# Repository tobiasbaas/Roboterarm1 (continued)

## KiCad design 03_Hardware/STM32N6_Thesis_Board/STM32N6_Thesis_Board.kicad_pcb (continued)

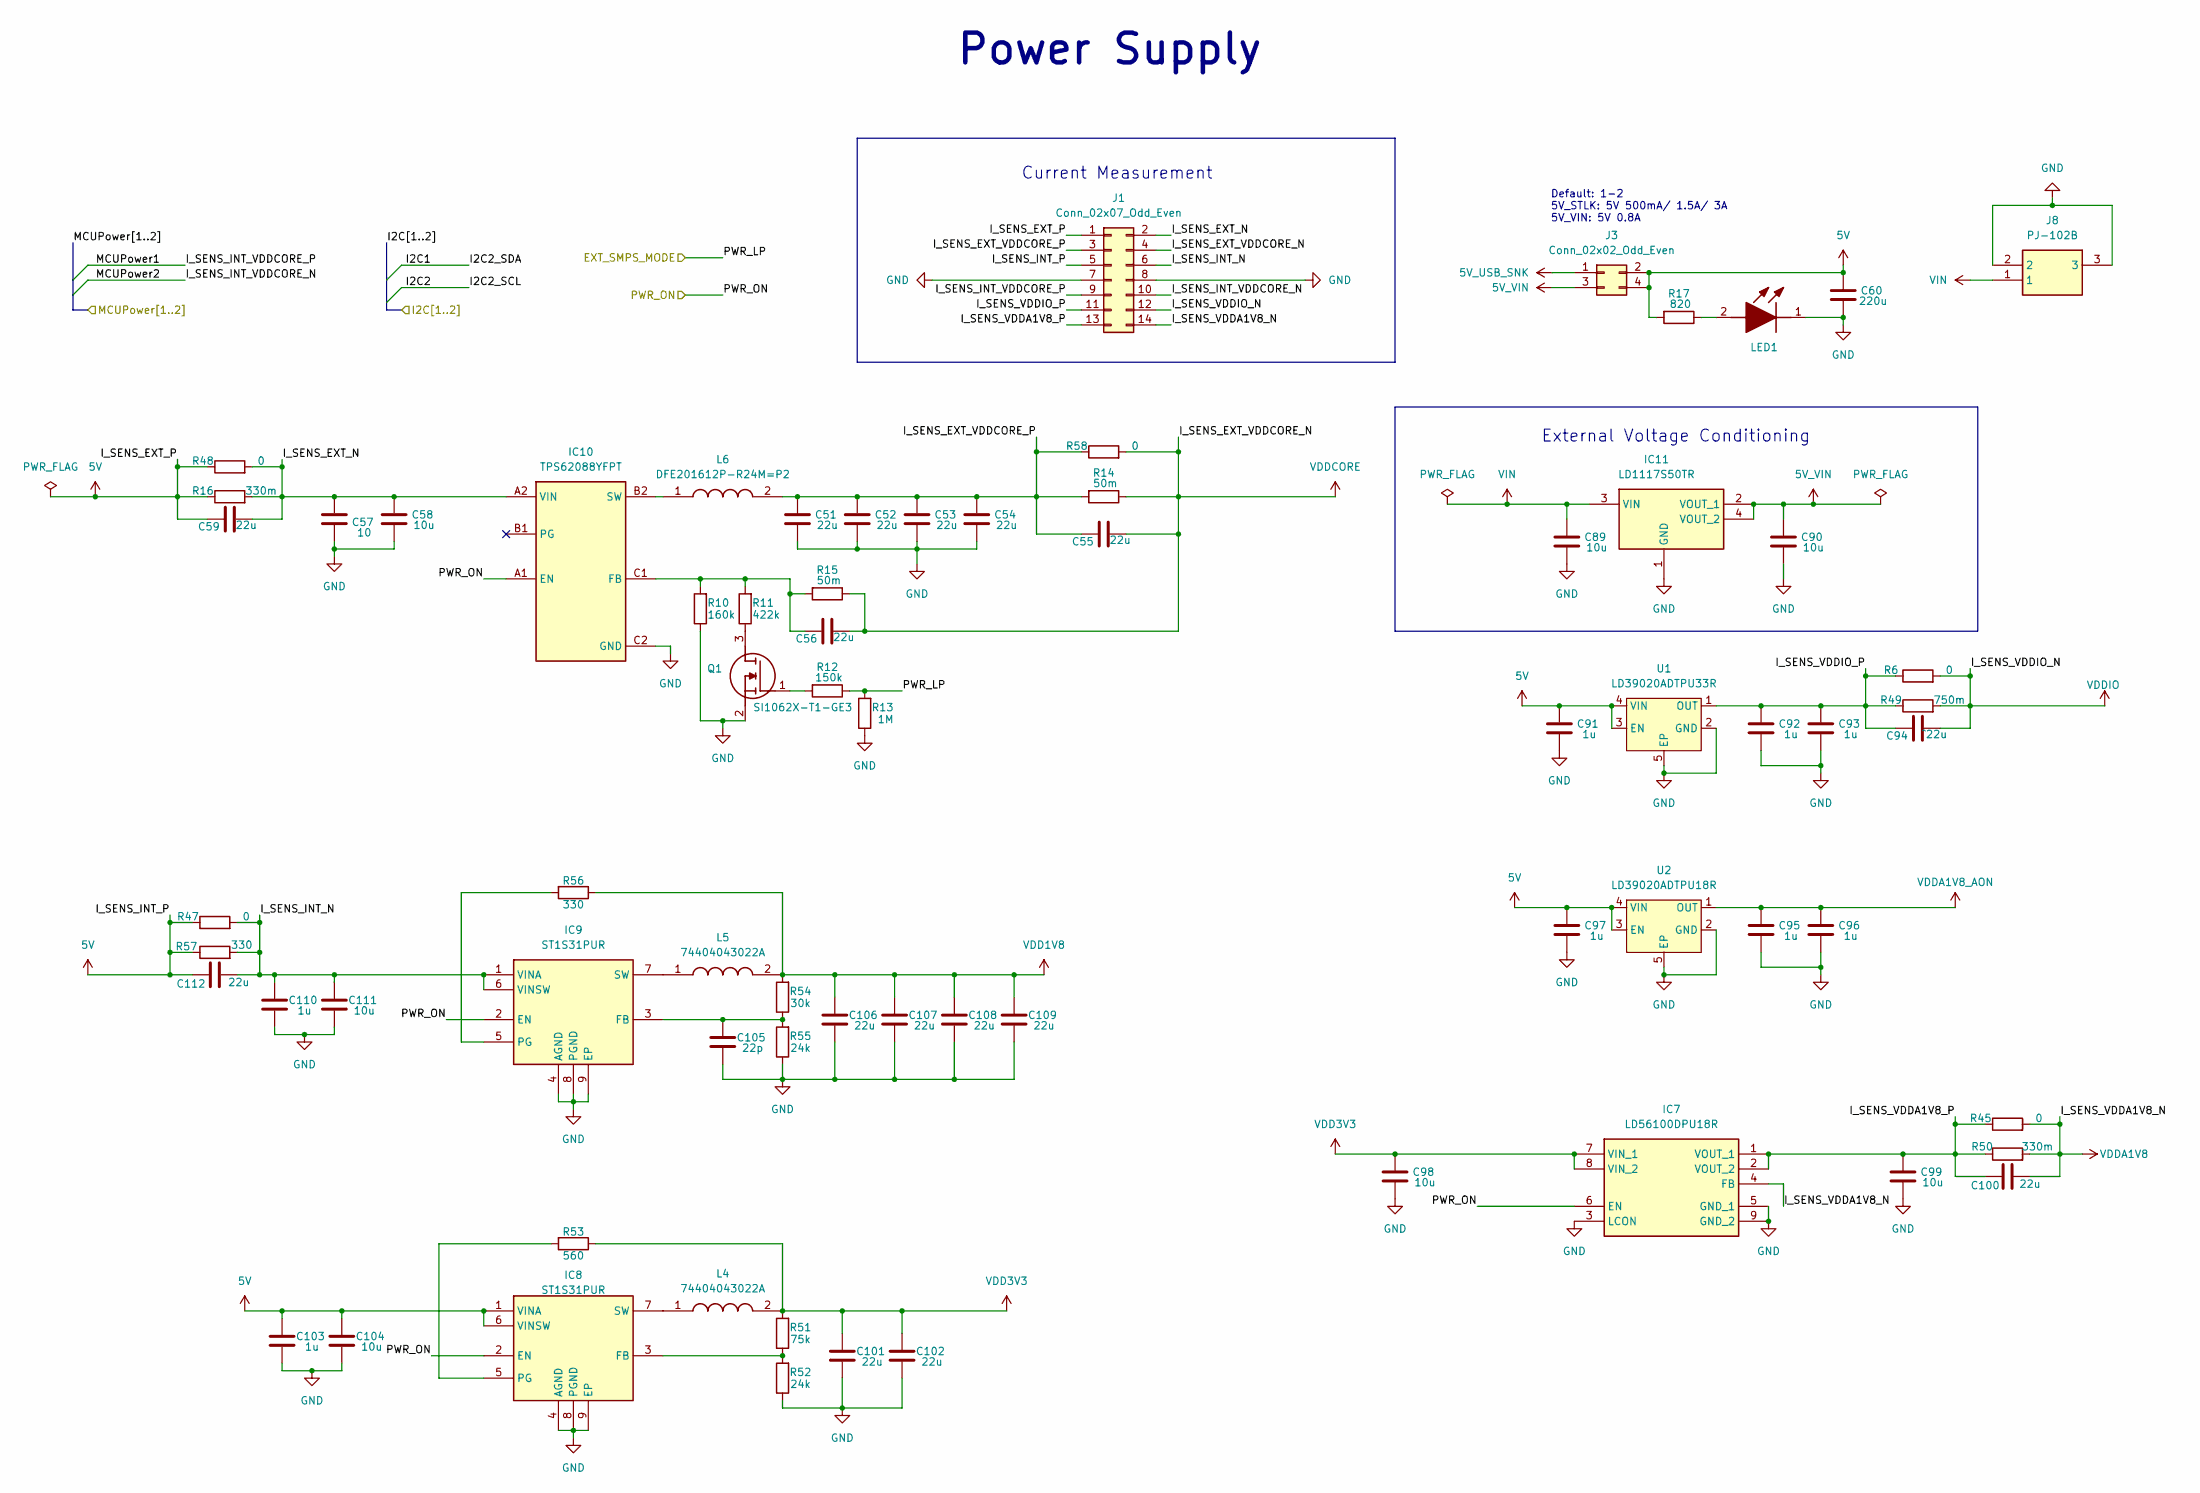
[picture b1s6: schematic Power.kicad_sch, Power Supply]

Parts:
C51, C52, C53, C54, C55, C56, C59, C100, C101, C102, C106, C107, C108, C109, C112: 22u; C_0603_1608Metric
C57: 10; C_0603_1608Metric
C58, C89, C90, C98, C99, C104, C111: 10u; C_0603_1608Metric
C60: 220u; C_0603_1608Metric
C91, C92, C93, C95, C96, C97, C103, C110: 1u; C_0603_1608Metric
C94: ^22u; C_0603_1608Metric
C105: 22p; C_0603_1608Metric
IC7: LD56100DPU18R; Mouser Part Number 511-LD56100DPU18R
IC8, IC9: ST1S31PUR; SON65P300X300X100-9N-D; Mouser Part Number 511-ST1S31PUR
IC10: TPS62088YFPT; BGA6C40P2X3_80X120X50; Mouser Part Number 595-TPS62088YFPT
IC11: LD1117S50TR; SOT230P700X190-4N; Mouser Part Number 511-LD1117S50
J1: Conn_02x07_Odd_Even; PinHeader_2x07_P2.54mm_Vertical
J3: Conn_02x02_Odd_Even; PinHeader_2x02_P2.54mm_Vertical
J8: PJ-102B; PJ102B; Mouser Part Number 490-PJ-102B
L4, L5: 74404043022A; INDPM4040X250N; Mouser Part Number 710-74404043022A
L6: DFE201612P-R24M=P2; 1286ASH1R0MP2; Mouser Part Number 81-DFE201612P-R24MP2
LED1: KG_EELP41.22-PHRH-35-A8J8-20-R18; KGEELP4122PHRH35A8J820R18; Mouser Part Number 720-P4122PHRH35A8J82
Q1: SI1062X-T1-GE3; SOTFL50P160X80-3N; Mouser Part Number 78-SI1062X-T1-GE3
R6, R45, R47, R48, R58: 0; R_0603_1608Metric
R10: 160k; R_0603_1608Metric
R11: 422k; R_0603_1608Metric
R12: 150k; R_0603_1608Metric
R13: 1M; R_0603_1608Metric
R14, R15: 50m; R_0603_1608Metric
R16, R50: 330m; R_0603_1608Metric
R17: 820; R_0603_1608Metric
R49: 750m; R_0603_1608Metric
R51: 75k; R_0603_1608Metric
R52, R55: 24k; R_0603_1608Metric
R53: 560; R_0603_1608Metric
R54: 30k; R_0603_1608Metric
R56, R57: 330; R_0603_1608Metric
U1: LD39020ADTPU33R; OnSemi_XDFN4-1EP_1.0x1.0mm_EP0.52x0.52mm
U2: LD39020ADTPU18R; OnSemi_XDFN4-1EP_1.0x1.0mm_EP0.52x0.52mm

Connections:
5V: C59.2, C60.2, C91.2, C97.2, C103.2, C104.2, C112.2, IC8.1 (VINA), IC8.6 (VINSW), J1.1, J1.5, J3.2, J3.4, R16.1, R17.2, R47.1, R48.1, R57.1, U1.3 (EN), U1.4 (VIN), U2.3 (EN), U2.4 (VIN); also elsewhere on the board
5V_USB_SNK: J3.1; also elsewhere on the board
5V_VIN: C90.2, IC11.2 (VOUT_1), IC11.4 (VOUT_2), J3.3
/Power/I_SENS_EXT_N: C57.2, C58.2, C59.1, IC10.A2 (VIN), J1.2, R16.2, R48.2
/Power/I_SENS_EXT_VDDCORE_P: C51.2, C52.2, C53.2, C54.2, C55.2, J1.3, L6.2, R14.2, R58.1
/Power/I_SENS_INT_N: C110.2, C111.2, C112.1, IC9.1 (VINA), IC9.6 (VINSW), J1.6, R47.2, R57.2
/Power/I_SENS_VDDA1V8_P: C99.2, C100.2, IC7.1 (VOUT_1), IC7.2 (VOUT_2), J1.13, R45.1, R50.1
/Power/I_SENS_VDDIO_P: C92.2, C93.2, C94.2, J1.11, R6.1, R49.1, U1.1 (OUT)
/Power/MCUPower1: J1.9; also elsewhere on the board
/Power/PWR_LP: R12.1, R13.2; also elsewhere on the board
/Power/PWR_ON: IC7.6 (EN), IC8.2 (EN), IC9.2 (EN), IC10.A1 (EN); also elsewhere on the board
GND: C51.1, C52.1, C53.1, C54.1, C57.1, C58.1, C60.1, C89.1, C90.1, C91.1, C92.1, C93.1, C95.1, C96.1, C97.1, C98.1, C99.1, C101.1, C102.1, C103.1, C104.1, C105.1, C106.1, C107.1, C108.1, C109.1, C110.1, C111.1, IC7.3 (LCON), IC7.5 (GND_1), IC7.9 (GND_2), IC8.4 (AGND), IC8.8 (PGND), IC8.9 (EP), IC9.4 (AGND), IC9.8 (PGND), IC9.9 (EP), IC10.C2 (GND), IC11.1 (GND), J1.7, J1.8, J8.2, J8.3, LED1.1 (K), Q1.2 (S), R10.1, R13.1, R52.1, R55.1, U1.2 (GND), U1.5 (EP), U2.2 (GND), U2.5 (EP); also elsewhere on the board
unnamed: IC8.3 (FB), R51.1, R52.2
unnamed: IC8.5 (PG), R53.2
unnamed: IC8.7 (SW), L4.1
unnamed: C105.2, IC9.3 (FB), R54.1, R55.2
unnamed: IC9.5 (PG), R56.2
unnamed: IC9.7 (SW), L5.1
unnamed: C56.2, IC10.C1 (FB), R10.2, R11.2, R15.2
unnamed: IC10.B2 (SW), L6.1
unnamed: LED1.2 (A), R17.1
unnamed: Q1.3 (D), R11.1
unnamed: Q1.1 (G), R12.2
VDD1V8: C106.2, C107.2, C108.2, C109.2, L5.2, R54.2, R56.1; also elsewhere on the board
VDD3V3: C98.2, C101.2, C102.2, IC7.7 (VIN_1), IC7.8 (VIN_2), L4.2, R51.2, R53.1; also elsewhere on the board
VDDA1V8: C100.1, IC7.4 (FB), J1.14, R45.2, R50.2; also elsewhere on the board
VDDA1V8_AON: C95.2, C96.2, U2.1 (OUT); also elsewhere on the board
VDDCORE: C55.1, C56.1, J1.4, J1.10, R14.1, R15.1, R58.2; also elsewhere on the board
VDDIO: C94.1, J1.12, R6.2, R49.2; also elsewhere on the board
VIN: C89.2, IC11.3 (VIN), J8.1

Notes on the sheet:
Current Measurement
Power Supply
Default: 1-2 5V_STLK: 5V 500mA/ 1.5A/ 3A 5V_VIN: 5V 0.8A
External Voltage Conditioning

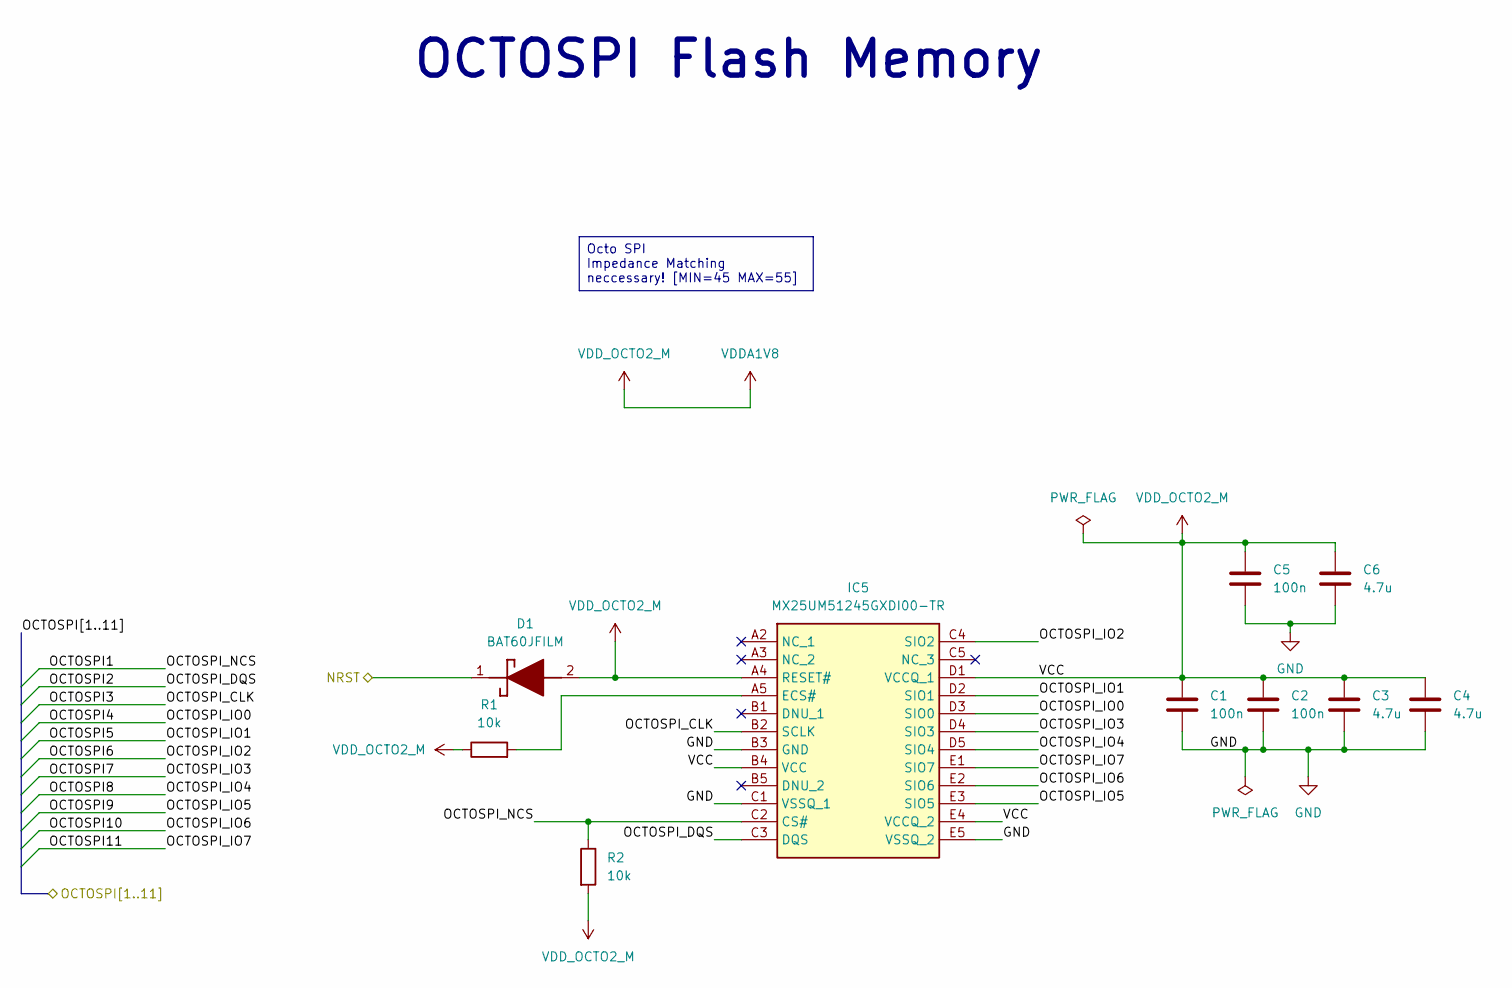
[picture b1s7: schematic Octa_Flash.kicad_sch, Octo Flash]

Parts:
C1, C2, C5: 100n; C_0603_1608Metric
C3, C4, C6: 4.7u; C_0603_1608Metric
D1: BAT60JFILM; SOD2513X117N; Mouser Part Number 511-BAT60JFILM
IC5: MX25UM51245GXDI00-TR; BGA24C100P5X5_600X800X120; Mouser Part Number 95-25UM51245GXDITR
R1, R2: 10k; R_0603_1608Metric

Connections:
/External Interface/NRST: D1.1 (K); also elsewhere on the board
/Octa_Flash/OCTOSPI1: IC5.C2 (CS#), R2.1; also elsewhere on the board
/Octa_Flash/OCTOSPI2: IC5.C3 (DQS); also elsewhere on the board
/Octa_Flash/OCTOSPI3: IC5.B2 (SCLK); also elsewhere on the board
/Octa_Flash/OCTOSPI4: IC5.D3 (SIO0); also elsewhere on the board
/Octa_Flash/OCTOSPI5: IC5.D2 (SIO1); also elsewhere on the board
/Octa_Flash/OCTOSPI6: IC5.C4 (SIO2); also elsewhere on the board
/Octa_Flash/OCTOSPI7: IC5.D4 (SIO3); also elsewhere on the board
/Octa_Flash/OCTOSPI8: IC5.D5 (SIO4); also elsewhere on the board
/Octa_Flash/OCTOSPI9: IC5.E3 (SIO5); also elsewhere on the board
/Octa_Flash/OCTOSPI10: IC5.E2 (SIO6); also elsewhere on the board
/Octa_Flash/OCTOSPI11: IC5.E1 (SIO7); also elsewhere on the board
GND: C1.2, C2.2, C3.2, C4.2, C5.2, C6.2, IC5.B3 (GND), IC5.C1 (VSSQ_1), IC5.E5 (VSSQ_2); also elsewhere on the board
unnamed: IC5.A5 (ECS#), R1.2
VDDA1V8: C1.1, C2.1, C3.1, C4.1, C5.1, C6.1, D1.2 (A), IC5.A4 (RESET#), IC5.B4 (VCC), IC5.D1 (VCCQ_1), IC5.E4 (VCCQ_2), R1.1, R2.2; also elsewhere on the board

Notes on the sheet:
OCTOSPI Flash Memory
Octo SPI Impedance Matching neccessary! [MIN=45 MAX=55]

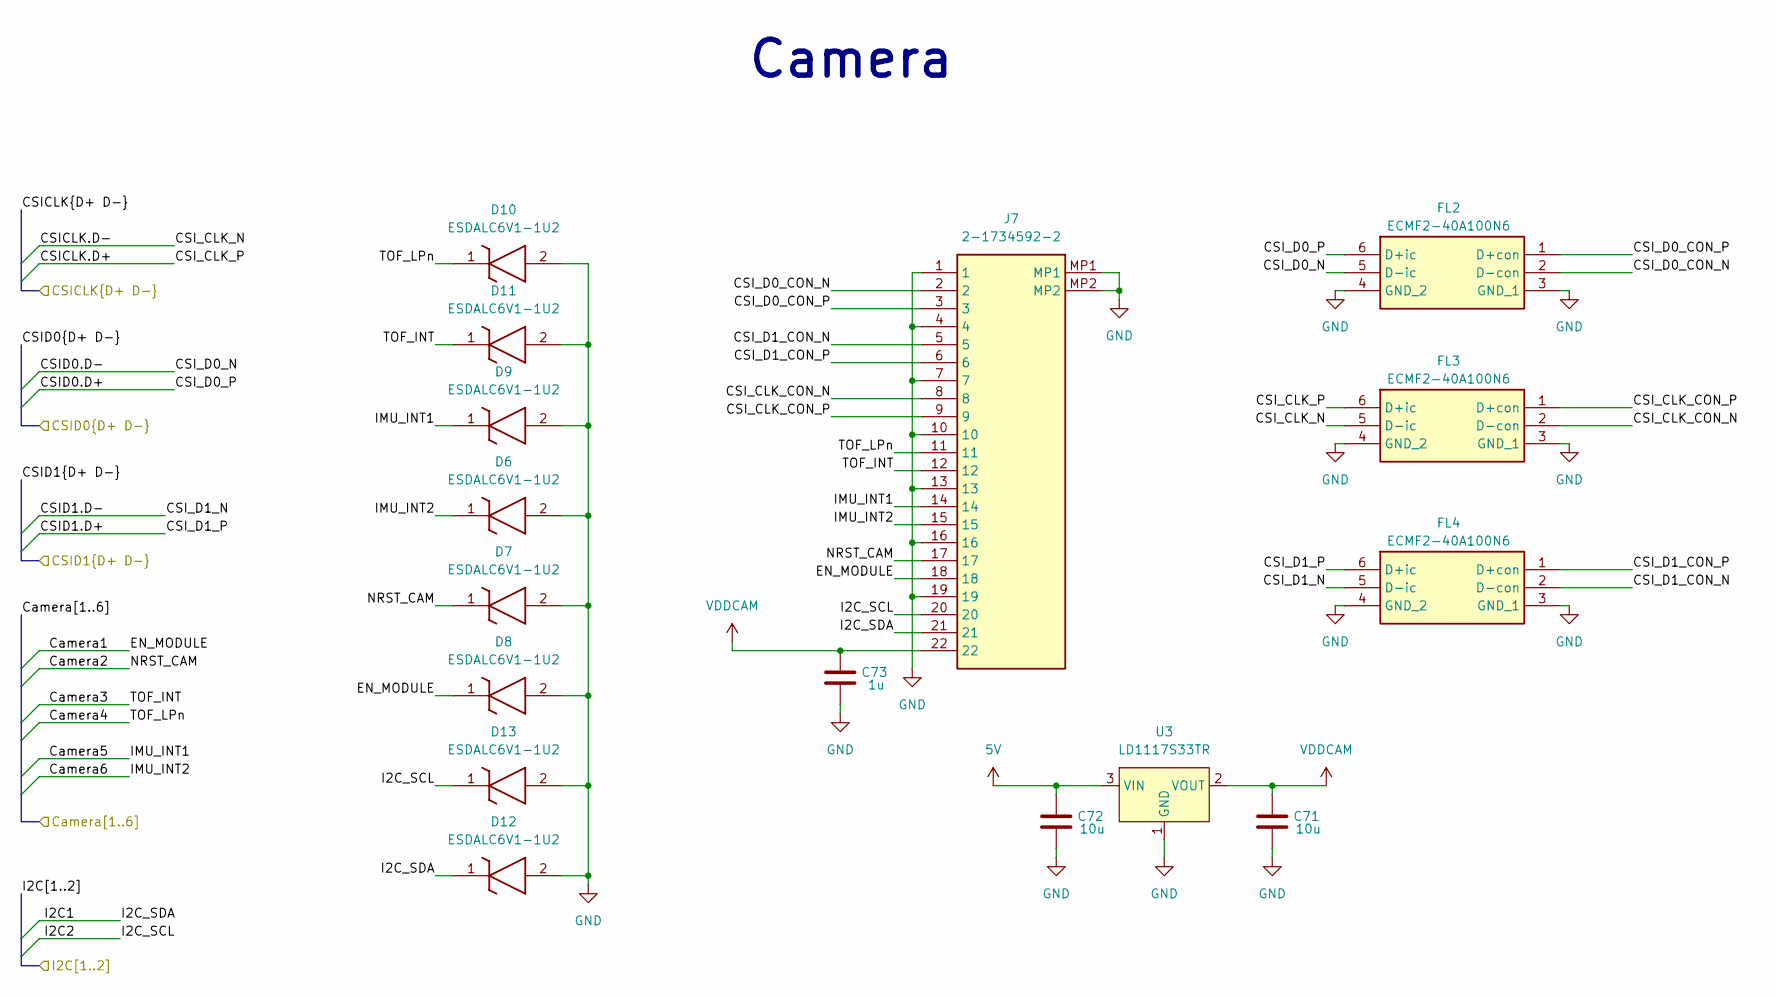
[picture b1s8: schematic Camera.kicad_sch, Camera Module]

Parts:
C71, C72: 10u; C_0603_1608Metric
C73: 1u; C_0603_1608Metric
D6, D7, D8, D9, D10, D11, D12, D13: ESDALC6V1-1U2; ESDALC6V11U2; Mouser Part Number 511-ESDALC6V1-1U2
FL2, FL3, FL4: ECMF2-40A100N6; ECMF240A100N6; Mouser Part Number 511-ECMF2-40A100N6
J7: 2-1734592-2; 217345922; Mouser Part Number 571-2-1734592-2
U3: LD1117S33TR; SOT-223-3_TabPin2

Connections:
5V: C72.2, U3.3 (VIN); also elsewhere on the board
/Camera/CSICLK.D+: FL3.6 (D+ic); also elsewhere on the board
/Camera/CSICLK.D-: FL3.5 (D-ic); also elsewhere on the board
/Camera/CSID0.D+: FL2.6 (D+ic); also elsewhere on the board
/Camera/CSID0.D-: FL2.5 (D-ic); also elsewhere on the board
/Camera/CSID1.D+: FL4.6 (D+ic); also elsewhere on the board
/Camera/CSID1.D-: FL4.5 (D-ic); also elsewhere on the board
/Camera/CSI_CLK_CON_N: FL3.2 (D-con), J7.8
/Camera/CSI_CLK_CON_P: FL3.1 (D+con), J7.9
/Camera/CSI_D0_CON_N: FL2.2 (D-con), J7.2
/Camera/CSI_D0_CON_P: FL2.1 (D+con), J7.3
/Camera/CSI_D1_CON_N: FL4.2 (D-con), J7.5
/Camera/CSI_D1_CON_P: FL4.1 (D+con), J7.6
/Camera/Camera3: D11.1 (K), J7.12; also elsewhere on the board
/Camera/Camera4: D10.1 (K), J7.11; also elsewhere on the board
/Camera/Camera5: D9.1 (K), J7.14; also elsewhere on the board
/Camera/Camera6: D6.1 (K), J7.15; also elsewhere on the board
/Camera/I2C1: D12.1 (K), J7.21; also elsewhere on the board
/Camera/I2C2: D13.1 (K), J7.20; also elsewhere on the board
GND: C71.1, C72.1, C73.1, D6.2 (A), D7.2 (A), D8.2 (A), D9.2 (A), D10.2 (A), D11.2 (A), D12.2 (A), D13.2 (A), FL2.3 (GND_1), FL2.4 (GND_2), FL3.3 (GND_1), FL3.4 (GND_2), FL4.3 (GND_1), FL4.4 (GND_2), J7.1, J7.4, J7.7, J7.10, J7.13, J7.16, J7.19, J7.MP1, J7.MP2, U3.1 (GND); also elsewhere on the board
VDDCAM: C71.2, C73.2, D7.1 (K), D8.1 (K), J7.17, J7.18, J7.22, U3.2 (VOUT); also elsewhere on the board

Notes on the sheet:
Camera

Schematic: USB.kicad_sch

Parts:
C65: 2.2u; C_0603_1608Metric
C66, C67: 330p; C_0603_1608Metric
C68: 100n; C_0603_1608Metric
C69: 10p; C_0603_1608Metric
D2: ESDA25P35-1U1M; ESDA25P351U1M; Mouser Part Number 511-ESDA25P35-1U1M
FL1: ECMF2-40A100N6; ECMF240A100N6; Mouser Part Number 511-ECMF2-40A100N6
IC2: TCPP03-M20; QFN50P400X400X80-21N-D; Mouser Part Number 511-TCPP03-M20
J4: 12401826E412A; Mouser Part Number 523-12401826E412A
LED2: KG_EELP41.22-PHRH-35-A8J8-20-R18; KGEELP4122PHRH35A8J820R18; Mouser Part Number 720-P4122PHRH35A8J82
LED3: LS_R976-NR-1; LEDC2012X40N; Mouser Part Number 720-LSR976-NR-1
Q2, Q5: STL40DN3LLH5; Mouser Part Number 511-STL40DN3LLH5
Q3, Q4: BSR14; SOT95P240X120-3N; Mouser Part Number 512-BSR14
R20, R27, R32: 10k; R_0603_1608Metric
R21, R26, R35: 100k; R_0603_1608Metric
R22: 24k; R_0603_1608Metric
R23, R25: 1.3M; R_0603_1608Metric
R24, R33: 22m; R_0603_1608Metric
R28, R34: 47k; R_0603_1608Metric
R29: 22k; R_0603_1608Metric
R30: 270; R_0603_1608Metric
R31: 140k; R_0603_1608Metric
R60, R61: 0; R_0603_1608Metric

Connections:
5V: Q5.5 (D1_1), Q5.6 (D1_2); also elsewhere on the board
5V_USB_SNK: Q2.5 (D1_1), Q2.6 (D1_2); also elsewhere on the board
/Camera/I2C1: R61.1; also elsewhere on the board
/Camera/I2C2: R60.1; also elsewhere on the board
/STM32N6_microcontroller/USB1: IC2.20 (EN), R26.2; also elsewhere on the board
/STM32N6_microcontroller/USB1HS.D+: FL1.6 (D+ic); also elsewhere on the board
/STM32N6_microcontroller/USB1HS.D-: FL1.5 (D-ic); also elsewhere on the board
/STM32N6_microcontroller/USB2: IC2.4 (IANA); also elsewhere on the board
/STM32N6_microcontroller/USB3: IC2.1 (CC1); also elsewhere on the board
/STM32N6_microcontroller/USB4: IC2.3 (CC2); also elsewhere on the board
/STM32N6_microcontroller/USB5: IC2.19 (FLGN), R27.1; also elsewhere on the board
/STM32N6_microcontroller/USB6: C69.2, R31.1, R32.2; also elsewhere on the board
/STM32N6_microcontroller/USB7: R34.1; also elsewhere on the board
/USB/D+: FL1.1 (D+con), J4.A6 (D+_1), J4.B6 (D+_2)
/USB/D-: FL1.2 (D-con), J4.A7 (D-_1), J4.B7 (D-_2)
GND: C65.1, C66.1, C67.1, C68.1, C69.1, D2.2 (A), FL1.3 (GND_1), FL1.4 (GND_2), IC2.12 (GND), IC2.21 (EP), J4.A1 (GND_1), J4.A12 (GND_2), J4.B1 (GND_3), J4.B12 (GND_4), J4.MH1, J4.MH2, J4.MH3, J4.MH4, Q3.2 (E), Q4.2 (E), R20.1, R22.2, R26.1, R29.2, R32.1, R35.2; also elsewhere on the board
unnamed: C68.2, IC2.14 (CBIAS)
unnamed: C66.2, IC2.15 (CC1C), J4.A5 (CC1)
unnamed: C67.2, IC2.13 (CC2C), J4.B5 (CC2)
unnamed: IC2.7 (GDCG), Q2.2 (G2), Q2.4 (G1), R25.1
unnamed: IC2.8 (GDCS), Q2.1 (S2), Q2.3 (S1), R25.2
unnamed: IC2.5 (GDPG), Q5.2 (G2), Q5.4 (G1), R23.1
unnamed: IC2.6 (GDPS), Q5.1 (S2), Q5.3 (S1), R23.2
unnamed: IC2.16 (I2C_ADD), R20.2
unnamed: IC2.10 (ISENSE), Q2.7 (D2_1), Q2.8 (D2_2), Q5.7 (D2_1), Q5.8 (D2_2), R24.2
unnamed: IC2.18 (SCL), R60.2
unnamed: IC2.17 (SDA), R61.2
unnamed: IC2.11 (VSENSE), R21.2, R22.1
unnamed: LED2.2 (A), R30.1
unnamed: LED2.1 (K), Q3.3 (C)
unnamed: LED3.2 (A), R33.2
unnamed: LED3.1 (K), Q4.3 (C)
unnamed: Q3.1 (B), R28.2, R29.1
unnamed: Q4.1 (B), R34.2, R35.1
VBUS: C65.2, D2.1 (K), IC2.9 (VBUSC), J4.A4 (VBUS_1), J4.A9 (VBUS_2), J4.B4 (VBUS_3), J4.B9 (VBUS_4), R21.1, R24.1, R28.1, R31.2
VDD3V3: IC2.2 (VCC_VCONN), R30.2, R33.1; also elsewhere on the board
VDDIO: R27.2; also elsewhere on the board

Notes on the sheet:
<- Sink Path
Diff Pair
5V_USB_LED
VBUS_SENSE
USB
Source Path ->
USB DP/DM should be routed in 90 ohm dff +/-10%

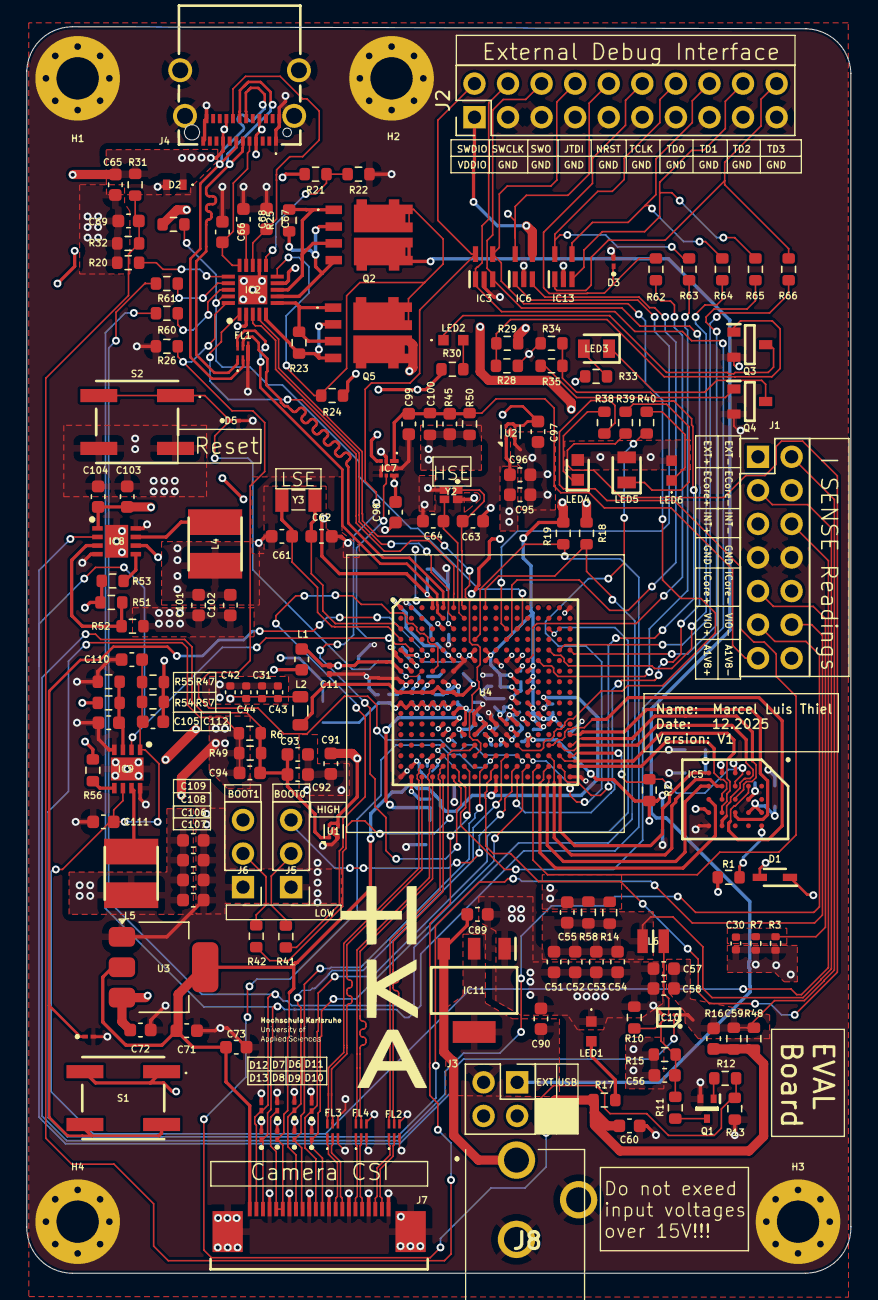
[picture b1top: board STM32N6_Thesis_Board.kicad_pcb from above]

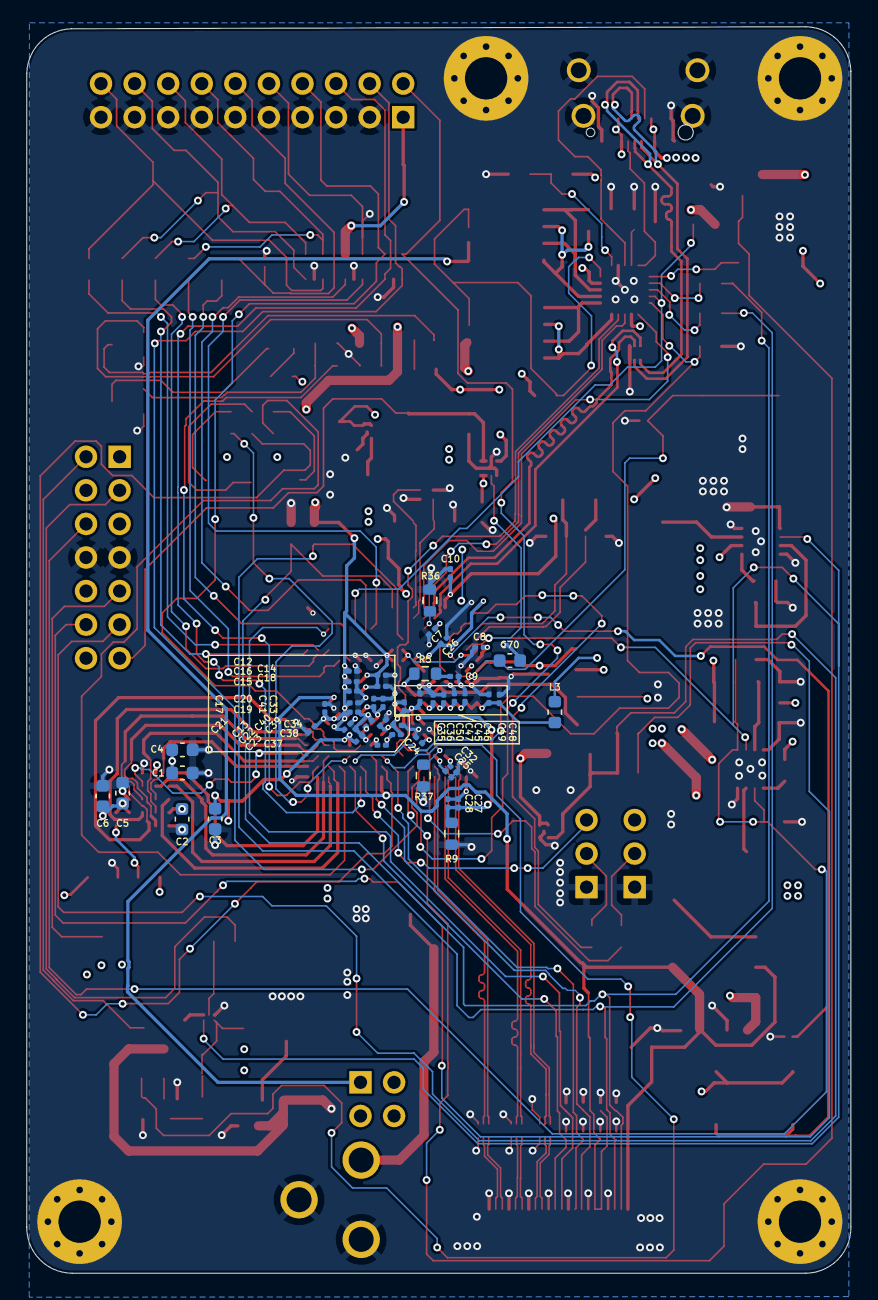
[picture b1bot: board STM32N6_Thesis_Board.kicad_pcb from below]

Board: 4 copper layers, 62.3 x 94.3 mm, 220 parts (49 on the bottom side), 131 nets.

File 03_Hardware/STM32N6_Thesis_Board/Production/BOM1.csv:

ID;Bezeichner;Footprint;Stückzahl;Bezeichnung;Anbieter und Referenz
1;FL3,FL2,FL1,FL4;ECMF240A100N6;4;ECMF2-40A100N6;
2;R50,R16;R_0603_1608Metric;2;330m;
3;R49;R_0603_1608Metric;1;750m;
4;R22,R55,R52;R_0603_1608Metric;3;24k;
5;R1,R32,R42,R41,R20,R2,R27,R5;R_0603_1608Metric;8;10k;
6;R66,R61,R6,R64,R60,R65,R47,R48,R63,R58,R45,R62,R9;R_0603_1608Metric;13;0;
7;U1;OnSemi_XDFN4-1EP_1.0x1.0mm_EP0.52x0.52mm;1;LD39020ADTPU33R;
8;C105;C_0603_1608Metric;1;22p;
9;R17;R_0603_1608Metric;1;820;
10;C106,C52,C53,C100,C109,C51,C102,C54,C59,C112,C108,C107,C101,C55,C56;C_0603_1608Metric;15;22u;
11;IC10;BGA6C40P2X3_80X120X50;1;TPS62088YFPT;
12;C96,C97,C91,C95,C93,C73,C103,C110,C92;C_0603_1608Metric;9;1u;
13;C42,C43,C30,C31,C44;C_0402_1005Metric;5;22u;
14;Q2,Q5;STL40DN3LLH5;2;STL40DN3LLH5;
15;R39,R57,R38,R40,R56;R_0603_1608Metric;5;330;
16;L6;1286ASH1R0MP2;1;DFE201612P-R24M=P2;
17;L2;L_0805_2012Metric;1;74479276168;
18;R18,R19;R_0603_1608Metric;2;1.5k;
19;C67,C66;C_0603_1608Metric;2;330p;
20;R3;R_0402_1005Metric;1;0;
21;IC9,IC8;SON65P300X300X100-9N-D;2;ST1S31PUR;
22;J4;12401826E412A;1;12401826E412A;
23;Q4,Q3;SOT95P240X120-3N;2;BSR14;
24;R53;R_0603_1608Metric;1;560;
25;C99,C89,C58,C98,C90,C104,C71,C111,C72;C_0603_1608Metric;9;10u;
26;D8,D10,D5,D3,D7,D4,D6,D9,D13,D11,D12;ESDALC6V11U2;11;ESDALC6V1-1U2;
27;R24,R33;R_0603_1608Metric;2;22m;
28;U4;BGA264C80P17X17_1400X1400X100;1;STM32N657X0H3Q;
29;IC11;SOT230P700X190-4N;1;LD1117S50TR;
30;J2;PinHeader_2x10_P2.54mm_Horizontal;1;Conn_02x10_Odd_Even;
31;J3;PinHeader_2x02_P2.54mm_Vertical;1;Conn_02x02_Odd_Even;
32;L4,L5;INDPM4040X250N;2;74404043022A;
33;R11;R_0603_1608Metric;1;422k;
34;R23,R25;R_0603_1608Metric;2;1.3M;
35;Q1;SOTFL50P160X80-3N;1;SI1062X-T1-GE3;
36;C57;C_0603_1608Metric;1;10;
37;R7;R_0402_1005Metric;1;50m;
38;J6,J5;PinHeader_1x03_P2.54mm_Vertical;2;Conn_01x03;
39;C61,C62;C_0603_1608Metric;2;2.2p;
40;R34,R28;R_0603_1608Metric;2;47k;
41;D1;SOD2513X117N;1;BAT60JFILM;
42;LED5,LED3;LEDC2012X40N;2;LS_R976-NR-1;
43;C65;C_0603_1608Metric;1;2.2u;
44;R29;R_0603_1608Metric;1;22k;
45;R51;R_0603_1608Metric;1;75k;
46;R21,R26,R35;R_0603_1608Metric;3;100k;
47;R54;R_0603_1608Metric;1;30k;
48;LED2,LED1,LED6;KGEELP4122PHRH35A8J820R18;3;KG_EELP41.22-PHRH-35-A8J8-20-R18;
49;C94;C_0603_1608Metric;1;22u;
50;R30;R_0603_1608Metric;1;270;
51;R15,R14;R_0603_1608Metric;2;50m;
52;C60;C_0603_1608Metric;1;220u;
53;U3;SOT-223-3_TabPin2;1;LD1117S33TR;
54;IC3,IC6,IC13;SOT65P210X110-5N;3;ESDALC6V1W5;
55;R10;R_0603_1608Metric;1;160k;
56;S1,S2;KSC721JLFS;2;KSC721J_LFS;
57;J1;PinHeader_2x07_P2.54mm_Vertical;1;Conn_02x07_Odd_Even;
58;IC7;LD56100DPU18R;1;LD56100DPU18R;
59;J8;PJ102B;1;PJ-102B;
60;C63,C64;C_0603_1608Metric;2;8.2p;
61;C68,C5,C1,C2;C_0603_1608Metric;4;100n;
62;LED4;LEDC1608X40N;1;LB_Q39G-L2OO-35-1;
63;J7;217345922;1;2-1734592-2;
64;U2;OnSemi_XDFN4-1EP_1.0x1.0mm_EP0.52x0.52mm;1;LD39020ADTPU18R;
65;IC2;QFN50P400X400X80-21N-D;1;TCPP03-M20;
66;C11,C49,C46,C19,C7,C23,C27,C26,C12,C21,C13,C16,C47,C18,C48,C24,C22,C15,C14,C17,C50,C25,C20,C45;C_0201_0603Metric;24;100n;
67;Y2;ABM12W300000MHZ6B1UT3;1;ABM12W-48.0000MHZ-7-D1X-T3;
68;R13;R_0603_1608Metric;1;1M;
69;D2;ESDA25P351U1M;1;ESDA25P35-1U1M;
70;Y3;CM7V32768TBQA020;1;CM7V-T1A-32.768KHZ-6PF-20PPM-TA-QC;
71;C69;C_0603_1608Metric;1;10p;
72;R31;R_0603_1608Metric;1;140k;
73;IC5;BGA24C100P5X5_600X800X120;1;MX25UM51245GXDI00-TR;
74;L1;L_0603_1608Metric;1;FBMJ1608HM180NTR;
75;R12;R_0603_1608Metric;1;150k;
76;L3;L_0603_1608Metric;1;LQW18AN2N2D10D;
77;C38,C35,C32,C39,C33,C37,C40,C10,C41,C34,C28,C36;C_0201_0603Metric;12;1u;
78;C6,C3,C4;C_0603_1608Metric;3;4.7u;
79;R36,R37;R_0603_1608Metric;2;200;
80;C8;C_0201_0603Metric;1;4.7u;
81;C70;C_0603_1608Metric;1;10n;
82;C9;C_0201_0603Metric;1;2.2n;

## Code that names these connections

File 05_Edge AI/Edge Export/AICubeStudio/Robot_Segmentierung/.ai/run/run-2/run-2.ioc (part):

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Mcu.Name=STM32N657X0HxQ
Mcu.Package=VFBGA264
Mcu.UserName=STM32N657X0HxQ
PA0.GPIOParameters=GPIO_Label,PinAttribute
PA0.GPIO_Label=LCD_G3
PA0.PinAttribute=FSBL
PA0.Signal=LTDC_G3
PA1.GPIOParameters=GPIO_Label,PinAttribute
PA1.GPIO_Label=LCD_G2
PA1.PinAttribute=FSBL
PA1.Signal=LTDC_G2
PA11.GPIOParameters=GPIO_Label,PinAttribute
PA11.GPIO_Label=UCPD1_VSENSE
PA11.PinAttribute=FSBL
PA11.Signal=ADC1_INP12
PA13(JTMS/SWDIO).GPIOParameters=GPIO_Label,PinAttribute
PA13(JTMS/SWDIO).GPIO_Label=SWDIO
PA13(JTMS/SWDIO).PinAttribute=FSBL
PA13(JTMS/SWDIO).Signal=DEBUG_JTMS-SWDIO
PA14(JTCK/SWCLK).GPIOParameters=GPIO_Label,PinAttribute
PA14(JTCK/SWCLK).GPIO_Label=SWCLK
PA14(JTCK/SWCLK).PinAttribute=FSBL
PA14(JTCK/SWCLK).Signal=DEBUG_JTCK-SWCLK
PA15(JTDI).GPIOParameters=GPIO_Label,PinAttribute
PA15(JTDI).GPIO_Label=LCD_R5
PA15(JTDI).PinAttribute=FSBL
PA15(JTDI).Signal=LTDC_R5
PA2.GPIOParameters=GPIO_Label,PinAttribute
PA2.GPIO_Label=LCD_B7
PA2.PinAttribute=FSBL
PA2.Signal=LTDC_B7
PA7.GPIOParameters=GPIO_Label,PinAttribute
PA7.GPIO_Label=LCD_B1
PA7.PinAttribute=FSBL
PA7.Signal=LTDC_B1
PA8.GPIOParameters=GPIO_Label,PinAttribute
PA8.GPIO_Label=LCD_B6
PA8.PinAttribute=FSBL
PA8.Signal=LTDC_B6
PB0.GPIOParameters=GPIO_Label,PinAttribute
PB0.GPIO_Label=SAI1_FS_A
PB0.PinAttribute=FSBL
PB0.Signal=SAI1_FS_A
PB1.ContextOwner=Appli
PB1.GPIOParameters=GPIO_Label,PinAttribute
PB1.GPIO_Label=AUDIO_RST
PB1.PinAttribute=Appli
PB1.Signal=GPIO_Output
PB11.GPIOParameters=GPIO_Label,PinAttribute
PB11.GPIO_Label=LCD_G6
PB11.PinAttribute=FSBL
PB11.Signal=LTDC_G6
PB12.GPIOParameters=GPIO_Label,PinAttribute
PB12.GPIO_Label=LCD_G5
PB12.PinAttribute=FSBL
PB12.Signal=LTDC_G5
PB14.GPIOParameters=GPIO_Label,PinAttribute
PB14.GPIO_Label=LCD_HSYNC
PB14.PinAttribute=FSBL
PB14.Signal=LTDC_HSYNC
PB15.GPIOParameters=GPIO_Label,PinAttribute
PB15.GPIO_Label=LCD_G4
PB15.PinAttribute=FSBL
PB15.Signal=LTDC_G4
PB2.GPIOParameters=GPIO_Label,PinAttribute
PB2.GPIO_Label=LCD_B2
PB2.PinAttribute=FSBL
PB2.Signal=LTDC_B2
PB4(NJTRST).GPIOParameters=GPIO_Label,PinAttribute
PB4(NJTRST).GPIO_Label=LCD_R3
PB4(NJTRST).PinAttribute=FSBL
PB4(NJTRST).Signal=LTDC_R3
PB5(JTDO/TRACESWO).GPIOParameters=GPIO_Label,PinAttribute
PB5(JTDO/TRACESWO).GPIO_Label=SWO
PB5(JTDO/TRACESWO).PinAttribute=FSBL
PB5(JTDO/TRACESWO).Signal=DEBUG_JTDO-SWO
PB6.GPIOParameters=GPIO_Label,PinAttribute
PB6.GPIO_Label=SAI1_CLK_A
PB6.PinAttribute=FSBL
PB6.Signal=SAI1_SCK_A
PB7.GPIOParameters=GPIO_Label,PinAttribute
PB7.GPIO_Label=SAI1_SD_A
PB7.PinAttribute=FSBL
PB7.Signal=SAI1_SD_A
PB9.ContextOwner=Appli
PB9.GPIOParameters=GPIO_Label,PinAttribute
PB9.GPIO_Label=PWR_USB2_EN
PB9.PinAttribute=Appli
PB9.Signal=GPIO_Output
PC0.GPIOParameters=GPIO_Label,PinAttribute
PC0.GPIO_Label=SD_D2
PC0.PinAttribute=FSBL
PC0.Signal=SDMMC2_D2
PC1.GPIOParameters=GPIO_Label,PinAttribute
PC1.GPIO_Label=I2C1_SDA
PC1.PinAttribute=FSBL
PC1.Signal=I2C1_SDA
PC13.ContextOwner=FSBL
PC13.GPIOParameters=GPIO_Label,PinAttribute
PC13.GPIO_Label=User
PC13.PinAttribute=FSBL
PC13.Signal=GPXTI13
PC14-OSC32_IN(OSC32_IN).GPIOParameters=PinAttribute
PC14-OSC32_IN(OSC32_IN).PinAttribute=Appli
PC14-OSC32_IN(OSC32_IN).Signal=RCC_OSC32_IN
PC15-OSC32_OUT(OSC32_OUT).GPIOParameters=PinAttribute
PC15-OSC32_OUT(OSC32_OUT).PinAttribute=Appli
PC15-OSC32_OUT(OSC32_OUT).Signal=RCC_OSC32_OUT
PC2.GPIOParameters=GPIO_Label,PinAttribute
PC2.GPIO_Label=SD_CK
PC2.PinAttribute=FSBL
PC2.Signal=SDMMC2_CK
PC3.GPIOParameters=GPIO_Label,PinAttribute
PC3.GPIO_Label=SD_CMD
PC3.PinAttribute=FSBL
PC3.Signal=SDMMC2_CMD
PC4.GPIOParameters=GPIO_Label,PinAttribute
PC4.GPIO_Label=SD_D0
PC4.PinAttribute=FSBL
PC4.Signal=SDMMC2_D0
PC5.GPIOParameters=GPIO_Label,PinAttribute
PC5.GPIO_Label=SD_D1
PC5.PinAttribute=FSBL
PC5.Signal=SDMMC2_D1
PC8.ContextOwner=Appli
PC8.GPIOParameters=GPIO_Label,PinAttribute
PC8.GPIO_Label=NRST_CAM
PC8.PinAttribute=Appli
PC8.Signal=GPIO_Input
PD1.GPIOParameters=PinAttribute
PD1.PinAttribute=ExtMemLoader
PD1.Signal=ETH1_MDC
PD10.ContextOwner=Appli
PD10.GPIOParameters=GPIO_Label,PinAttribute
PD10.GPIO_Label=USB1_INT
PD10.PinAttribute=Appli
PD10.Signal=GPIO_Input
PD12.GPIOParameters=PinAttribute
PD12.PinAttribute=ExtMemLoader
PD12.Signal=ETH1_MDIO
PD14.GPIOParameters=GPIO_Label,PinAttribute
PD14.GPIO_Label=I2C2_SCL
PD14.PinAttribute=FSBL
PD14.Signal=I2C2_SCL
PD15.GPIOParameters=GPIO_Label,PinAttribute
PD15.GPIO_Label=LCD_R2
PD15.PinAttribute=FSBL
PD15.Signal=LTDC_R2
PD2.ContextOwner=Appli
PD2.GPIOParameters=GPIO_Label,PinAttribute
PD2.GPIO_Label=EN_MODULE
PD2.PinAttribute=Appli
PD2.Signal=GPIO_Output
PD3.GPIOParameters=GPIO_Label,PinAttribute
PD3.GPIO_Label=ETH_MDINT
PD3.PinAttribute=ExtMemLoader
PD3.Signal=ETH1_PHY_INTN
PD4.GPIOParameters=GPIO_Label,PinAttribute
PD4.GPIO_Label=I2C2_SDA
PD4.PinAttribute=FSBL
PD4.Signal=I2C2_SDA
PD8.GPIOParameters=GPIO_Label,PinAttribute
PD8.GPIO_Label=LCD_R7
PD8.PinAttribute=FSBL
PD8.Signal=LTDC_R7
PD9.GPIOParameters=GPIO_Label,PinAttribute
PD9.GPIO_Label=LCD_R1
PD9.PinAttribute=FSBL
PD9.Signal=LTDC_R1
PE0.GPIOParameters=GPIO_Label,PinAttribute
PE0.GPIO_Label=TAMP
PE0.PinAttribute=FSBL
PE0.Signal=TAMP_IN6
PE1.ContextOwner=Appli
PE1.GPIOParameters=GPIO_Label,PinAttribute
PE1.GPIO_Label=LCD_NRST
PE1.PinAttribute=Appli
PE1.Signal=GPIO_Output
PE11.GPIOParameters=GPIO_Label,PinAttribute
PE11.GPIO_Label=LCD_VSYNC
PE11.PinAttribute=FSBL
PE11.Signal=LTDC_VSYNC
PE2.GPIOParameters=GPIO_Label,PinAttribute
PE2.GPIO_Label=MIC_CK
PE2.PinAttribute=FSBL
PE2.Signal=MDF1_CCK0
PE3.GPIOParameters=GPIO_Label,PinAttribute
PE3.GPIO_Label=SAI1_SD_B
PE3.PinAttribute=FSBL
PE3.Signal=SAI1_SD_B
PE4.GPIOParameters=GPIO_Label,PinAttribute
PE4.GPIO_Label=SD_D3
PE4.PinAttribute=FSBL
PE4.Signal=SDMMC2_D3
PE5.GPIOParameters=GPIO_Label,PinAttribute
PE5.GPIO_Label=VCP_TX
PE5.Mode=Asynchronous
PE5.PinAttribute=Appli
PE5.Signal=USART1_TX
PE6.GPIOParameters=GPIO_PuPd,GPIO_Label,PinAttribute
PE6.GPIO_Label=VCP_RX
PE6.GPIO_PuPd=GPIO_PULLUP
PE6.Mode=Asynchronous
PE6.PinAttribute=Appli
PE6.Signal=USART1_RX
PE7.GPIOParameters=PinAttribute
PE7.PinAttribute=FSBL
PE7.Signal=MDF1_CKI0
PE8.GPIOParameters=GPIO_Label,PinAttribute
PE8.GPIO_Label=MIC_D1
PE8.PinAttribute=FSBL
PE8.Signal=MDF1_SDI0
PF0.GPIOParameters=GPIO_Label,PinAttribute
PF0.GPIO_Label=ETH_GTX_CLK
PF0.PinAttribute=ExtMemLoader
PF0.Signal=ETH1_RGMII_GTX_CLK
PF10.GPIOParameters=PinAttribute
PF10.PinAttribute=ExtMemLoader
PF10.Signal=ETH1_RGMII_RX_CTL
PF11.GPIOParameters=PinAttribute
PF11.PinAttribute=ExtMemLoader
PF11.Signal=ETH1_RGMII_TX_CTL
PF12.GPIOParameters=PinAttribute
PF12.PinAttribute=ExtMemLoader
PF12.Signal=ETH1_RGMII_TXD0
PF13.GPIOParameters=PinAttribute
PF13.PinAttribute=ExtMemLoader
PF13.Signal=ETH1_RGMII_TXD1
PF14.GPIOParameters=PinAttribute
PF14.PinAttribute=ExtMemLoader
PF14.Signal=ETH1_RGMII_RXD0
PF15.GPIOParameters=PinAttribute
PF15.PinAttribute=ExtMemLoader
PF15.Signal=ETH1_RGMII_RXD1
PF2.GPIOParameters=GPIO_Label,PinAttribute
PF2.GPIO_Label=ETH_CLK125
PF2.PinAttribute=ExtMemLoader
PF2.Signal=ETH1_RGMII_CLK125
PF4.ContextOwner=FSBL
PF4.GPIOParameters=GPIO_Label,PinAttribute
PF4.GPIO_Label=SMPS_OVD
PF4.PinAttribute=FSBL
PF4.Signal=GPIO_Output
PF5.GPIOParameters=GPIO_Label,PinAttribute
PF5.GPIO_Label=ETH_CLK
PF5.PinAttribute=ExtMemLoader
PF5.Signal=ETH1_CLK
PF7.GPIOParameters=PinAttribute
PF7.PinAttribute=ExtMemLoader
PF7.Signal=ETH1_RGMII_RX_CLK
PF8.GPIOParameters=GPIO_Label,PinAttribute
PF8.GPIO_Label=ETH_RXD2
PF8.PinAttribute=ExtMemLoader
PF8.Signal=ETH1_RGMII_RXD2
PF9.GPIOParameters=GPIO_Label,PinAttribute
PF9.GPIO_Label=ETH_RXD3
PF9.PinAttribute=ExtMemLoader
PF9.Signal=ETH1_RGMII_RXD3
PG0.GPIOParameters=GPIO_Label,PinAttribute
PG0.GPIO_Label=LCD_R0
PG0.PinAttribute=FSBL
PG0.Signal=LTDC_R0
PG1.GPIOParameters=GPIO_Label,PinAttribute
PG1.GPIO_Label=LCD_G1
PG1.PinAttribute=FSBL
PG1.Signal=LTDC_G1
PG10.ContextOwner=Appli
PG10.GPIOParameters=GPIO_Label,PinAttribute
PG10.GPIO_Label=LED2
PG10.PinAttribute=Appli
PG10.Signal=GPIO_Input
PG11.GPIOParameters=GPIO_Label,PinAttribute
PG11.GPIO_Label=LCD_R6
PG11.PinAttribute=FSBL
PG11.Signal=LTDC_R6
PG12.GPIOParameters=GPIO_Label,PinAttribute
PG12.GPIO_Label=LCD_G0
PG12.PinAttribute=FSBL
PG12.Signal=LTDC_G0
PG13.GPIOParameters=GPIO_Label,PinAttribute
PG13.GPIO_Label=LCD_DE
PG13.PinAttribute=FSBL
PG13.Signal=LTDC_DE
PG15.GPIOParameters=GPIO_Label,PinAttribute
PG15.GPIO_Label=LCD_B0
PG15.PinAttribute=FSBL
PG15.Signal=LTDC_B0
PG3.GPIOParameters=GPIO_Label,PinAttribute
PG3.GPIO_Label=ETH_TX2
PG3.PinAttribute=ExtMemLoader
PG3.Signal=ETH1_RGMII_TXD2
PG4.GPIOParameters=GPIO_Label,PinAttribute
PG4.GPIO_Label=ETH_TXD3
PG4.PinAttribute=ExtMemLoader
PG4.Signal=ETH1_RGMII_TXD3
PG6.GPIOParameters=GPIO_Label,PinAttribute
PG6.GPIO_Label=LCD_B3
PG6.PinAttribute=FSBL
PG6.Signal=LTDC_B3
PG7.GPIOParameters=GPIO_Label,PinAttribute
PG7.GPIO_Label=SAI1_MCLK_A
PG7.PinAttribute=FSBL
PG7.Signal=SAI1_MCLK_A
PG8.GPIOParameters=GPIO_Label,PinAttribute
PG8.GPIO_Label=LCd_G7
PG8.PinAttribute=FSBL
PG8.Signal=LTDC_G7
PH0-OSC_IN(PH0).GPIOParameters=GPIO_Label,PinAttribute
PH0-OSC_IN(PH0).GPIO_Label=OSC_IN

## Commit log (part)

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2026-03-19 Neuer Initialier Commit
2026-03-19 STM: Funktionierenden STM Zwischenstand pushen
2026-03-20 Vorbereiten für neuen Commit
2026-03-20 Edge AI: Ändern des Blender Skriptes. Es gibt nun zwei. Das erste nimmt die Spheren für die Keypoints und berechnet nach händischer Korrektur die Offsets. Das zweite ist eine abgeänderte Version für 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
2026-03-23 Vorberietung des nächsten Push
2026-03-23 EdgeAI: Relative Pfade, Blender relative Positionsmitgabe, Änderung der Jypter Notebook
2026-03-25 Vorbereitung für den nächsten Push
2026-03-25 Edge AI: Neue quantisierte Version beider Modelle Segmentierung und Posenschätzung STM: Finales Image kreeieren, bevor Integration mit Edge AI Modellen
2026-03-27 Vorberreiten für neuen Psuh
2026-04-10 Build-Ordner aus der Versionierung entfernt
2026-04-10 Checkpoint STM32N6
2026-04-13 KI-Code: Änderungen im Validierungsskript Jupyter, damit nun die Winkel ausgegeben werden können. Die Winkel werden nicht per KI ermittelt, sondern über die Segmentierung und oder Keypoints berechnet
2026-04-13 KI-Code: Validerieung Jupyter Notebook wurde etwas angepasst. Keine nennesweriten Logikänderungen
